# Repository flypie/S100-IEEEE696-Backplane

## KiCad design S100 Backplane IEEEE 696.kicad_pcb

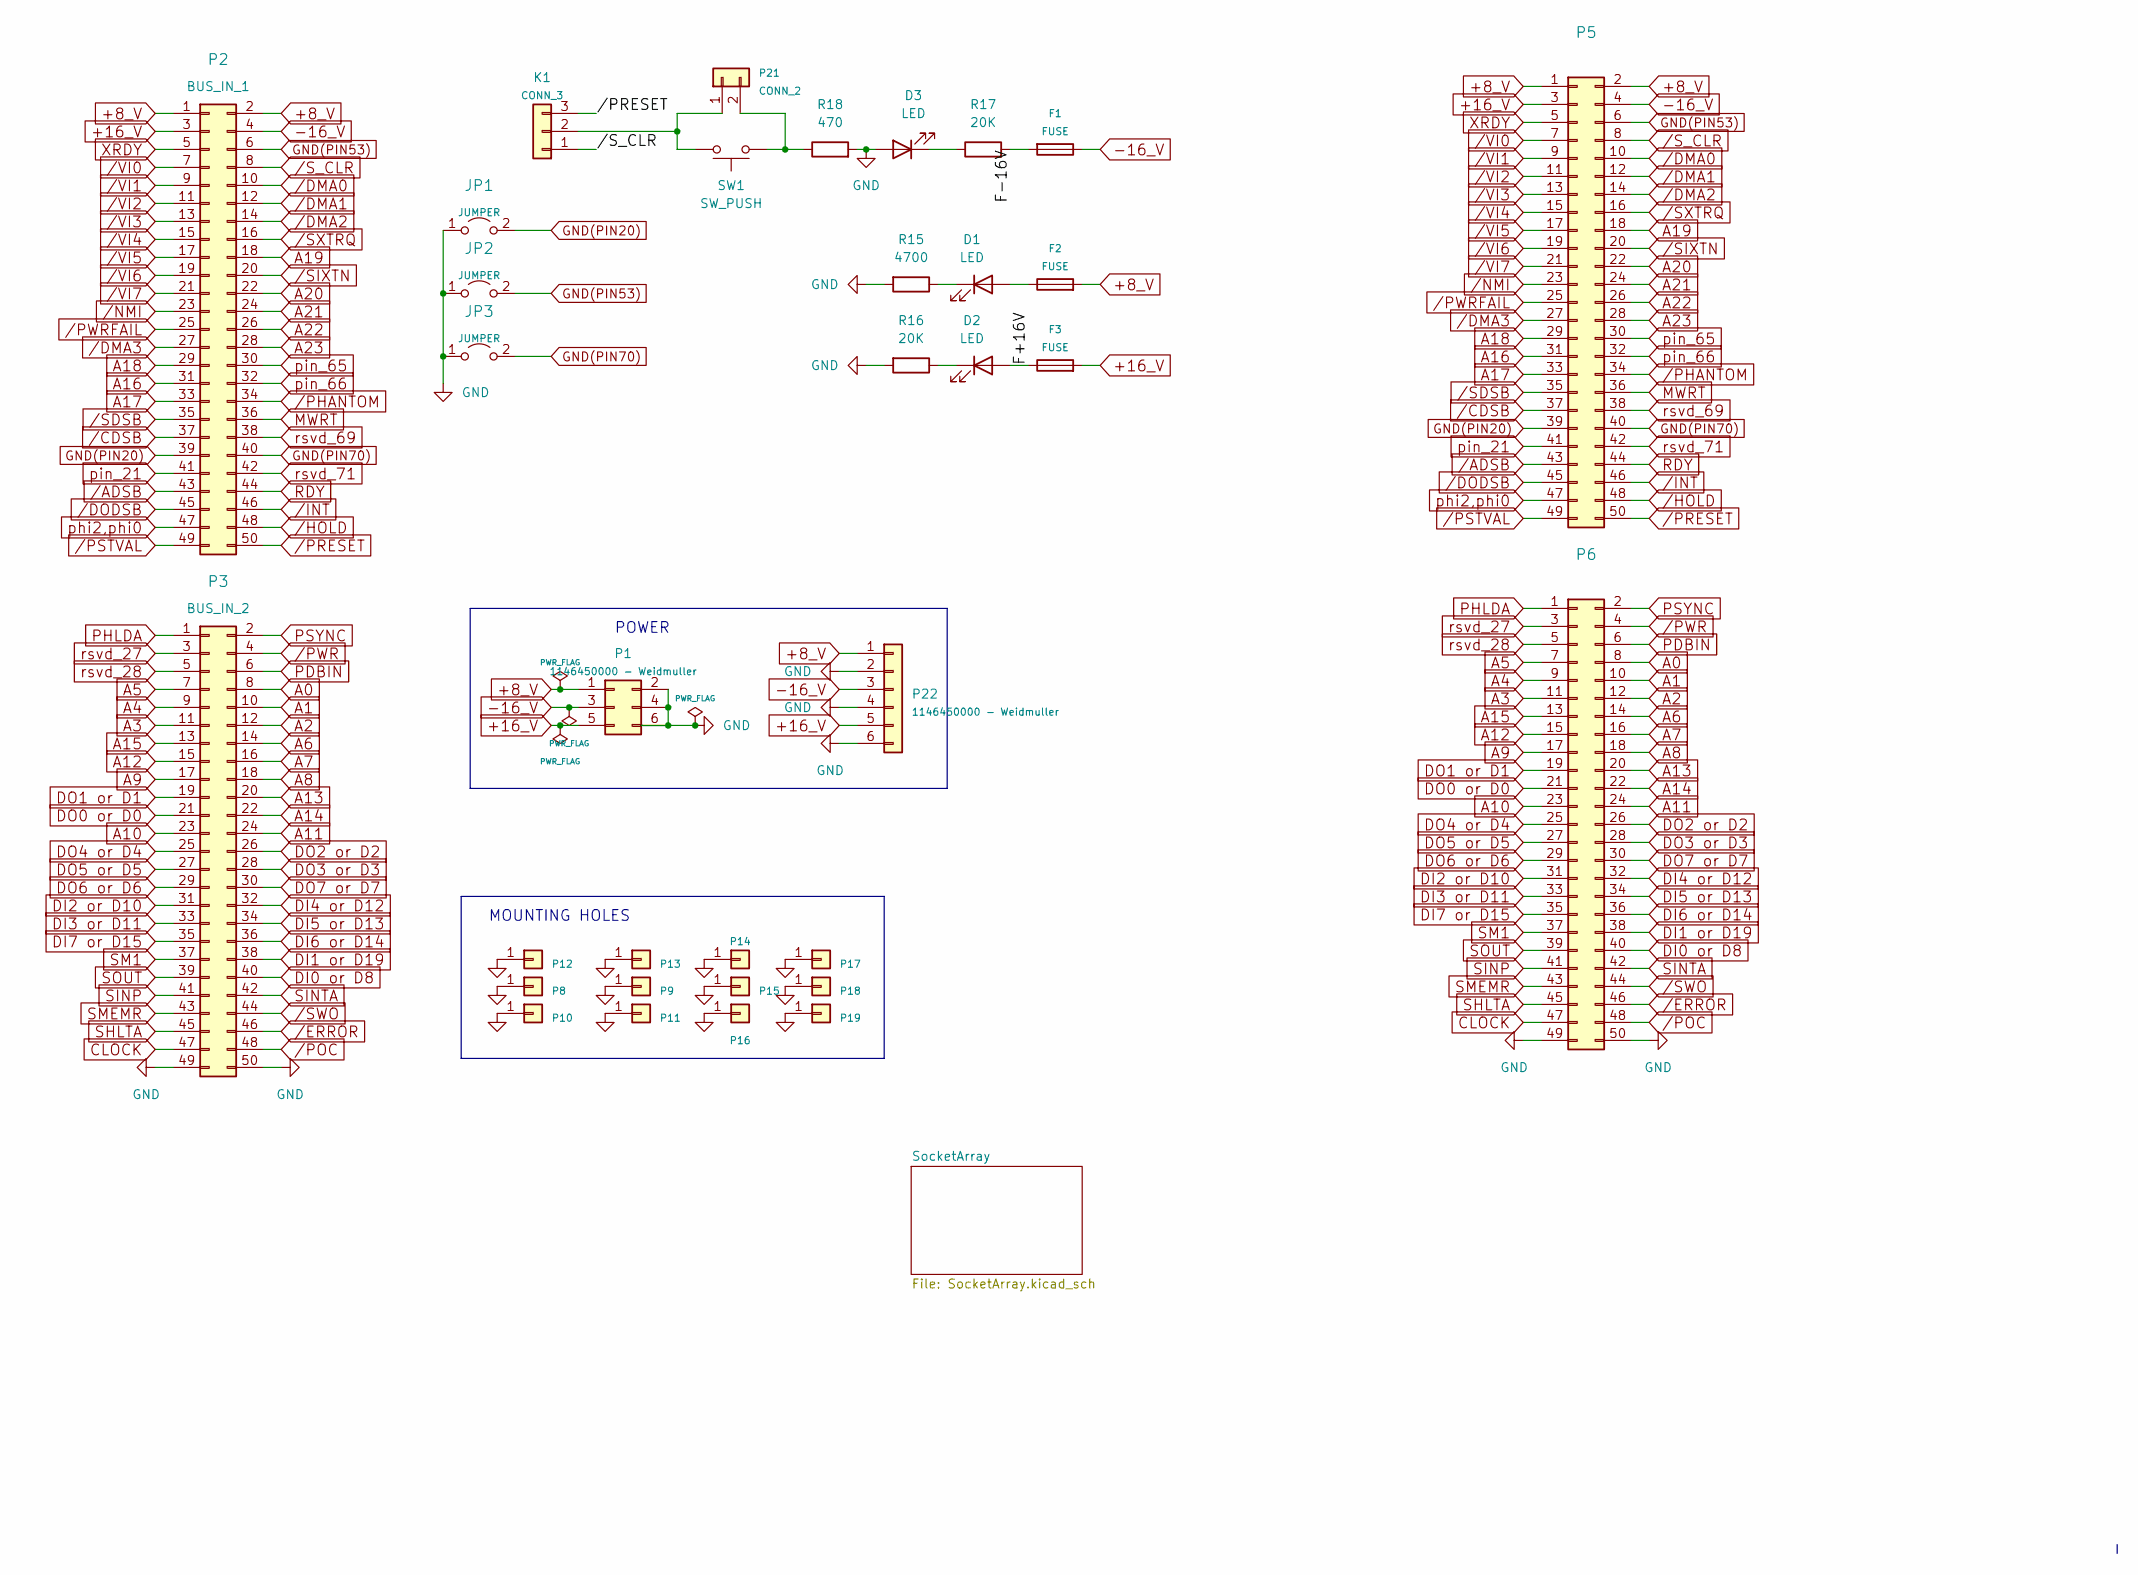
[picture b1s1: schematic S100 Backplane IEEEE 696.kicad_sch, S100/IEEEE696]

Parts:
D1, D2, D3: LED; LED_D3.0mm
F1, F2, F3: FUSE; R_Axial_DIN0207_L6.3mm_D2.5mm_P10.16mm_Horizontal
JP1, JP2, JP3: JUMPER; PinHeader_1x02_P2.54mm_Vertical
K1: CONN_3; PinHeader_1x03_P2.54mm_Vertical
P1, P22: 1146450000 - Weidmuller; 1146450000
P2: BUS_IN_1; PinHeader_2x25_P2.54mm_Vertical
P3: BUS_IN_2; PinHeader_2x25_P2.54mm_Vertical
P5, P6: PinHeader_2x25_P2.54mm_Vertical
P8, P9, P10, P11, P12, P13, P14, P15, P16, P17, P18, P19: CONN_1; MountingHole_3.5mm_Pad
P21: CONN_2; PinHeader_1x02_P2.54mm_Vertical
R15: 4700; R_Axial_DIN0207_L6.3mm_D2.5mm_P10.16mm_Horizontal
R16, R17: 20K; R_Axial_DIN0207_L6.3mm_D2.5mm_P10.16mm_Horizontal
R18: 470; R_Axial_DIN0207_L6.3mm_D2.5mm_P7.62mm_Horizontal
SW1: SW_PUSH; SW_PUSH_6mm_H7.3mm

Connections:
+8_V: F2.2, P1.1, P2.1, P2.2, P5.1, P5.2, P22.1; also elsewhere on the board
+16_V: F3.2, P1.5, P2.3, P5.3, P22.5; also elsewhere on the board
-16_V: F1.1, P1.3, P2.4, P5.4, P22.3; also elsewhere on the board
/F+16V: D2.2 (A), F3.1
/F-16V: F1.2, R17.2
A0: P3.8, P6.8; also elsewhere on the board
A1: P3.10, P6.10; also elsewhere on the board
A2: P3.12, P6.12; also elsewhere on the board
A3: P3.11, P6.11; also elsewhere on the board
A4: P3.9, P6.9; also elsewhere on the board
A5: P3.7, P6.7; also elsewhere on the board
A6: P3.14, P6.14; also elsewhere on the board
A7: P3.16, P6.16; also elsewhere on the board
A8: P3.18, P6.18; also elsewhere on the board
A9: P3.17, P6.17; also elsewhere on the board
A10: P3.23, P6.23; also elsewhere on the board
A11: P3.24, P6.24; also elsewhere on the board
A12: P3.15, P6.15; also elsewhere on the board
A13: P3.20, P6.20; also elsewhere on the board
A14: P3.22, P6.22; also elsewhere on the board
A15: P3.13, P6.13; also elsewhere on the board
A16: P2.31, P5.31; also elsewhere on the board
A17: P2.33, P5.33; also elsewhere on the board
A18: P2.29, P5.29; also elsewhere on the board
A19: P2.18, P5.18; also elsewhere on the board
A20: P2.22, P5.22; also elsewhere on the board
A21: P2.24, P5.24; also elsewhere on the board
A22: P2.26, P5.26; also elsewhere on the board
A23: P2.28, P5.28; also elsewhere on the board
CLOCK: P3.47, P6.47; also elsewhere on the board
DI0 or D8: P3.40, P6.40; also elsewhere on the board
DI1 or D19: P3.38, P6.38; also elsewhere on the board
DI2 or D10: P3.31, P6.31; also elsewhere on the board
DI3 or D11: P3.33, P6.33; also elsewhere on the board
DI4 or D12: P3.32, P6.32; also elsewhere on the board
DI5 or D13: P3.34, P6.34; also elsewhere on the board
DI6 or D14: P3.36, P6.36; also elsewhere on the board
DI7 or D15: P3.35, P6.35; also elsewhere on the board
DO0 or D0: P3.21, P6.21; also elsewhere on the board
DO1 or D1: P3.19, P6.19; also elsewhere on the board
DO2 or D2: P3.26, P6.26; also elsewhere on the board
DO3 or D3: P3.28, P6.28; also elsewhere on the board
DO4 or D4: P3.25, P6.25; also elsewhere on the board
DO5 or D5: P3.27, P6.27; also elsewhere on the board
DO6 or D6: P3.29, P6.29; also elsewhere on the board
DO7 or D7: P3.30, P6.30; also elsewhere on the board
GND(PIN20): JP1.2 (B), P2.39, P5.39; also elsewhere on the board
GND(PIN53): JP2.2 (B), P2.6, P5.6; also elsewhere on the board
GND(PIN70): JP3.2 (B), P2.40, P5.40; also elsewhere on the board
MWRT: P2.36, P5.36; also elsewhere on the board
unnamed: D1.1 (K), R15.1
unnamed: D1.2 (A), F2.1
unnamed: D2.1 (K), R16.1
unnamed: D3.1 (K), R17.1
unnamed: K1.2, P21.1, SW1.2
unnamed: P21.2, R18.1, SW1.1
PDBIN: P3.6, P6.6; also elsewhere on the board
PHLDA: P3.1, P6.1; also elsewhere on the board
PSYNC: P3.2, P6.2; also elsewhere on the board
RDY: P2.44, P5.44; also elsewhere on the board
SHLTA: P3.45, P6.45; also elsewhere on the board
SINP: P3.41, P6.41; also elsewhere on the board
SINTA: P3.42, P6.42; also elsewhere on the board
SM1: P3.37, P6.37; also elsewhere on the board
SMEMR: P3.43, P6.43; also elsewhere on the board
SOUT: P3.39, P6.39; also elsewhere on the board
XRDY: P2.5, P5.5; also elsewhere on the board
phi2,phi0: P2.47, P5.47; also elsewhere on the board
pin_21: P2.41, P5.41; also elsewhere on the board
pin_65: P2.30, P5.30; also elsewhere on the board
pin_66: P2.32, P5.32; also elsewhere on the board
rsvd_27: P3.3, P6.3; also elsewhere on the board
rsvd_28: P3.5, P6.5; also elsewhere on the board
rsvd_69: P2.38, P5.38; also elsewhere on the board
rsvd_71: P2.42, P5.42; also elsewhere on the board
/ADSB: P2.43, P5.43; also elsewhere on the board
/CDSB: P2.37, P5.37; also elsewhere on the board
/DMA0: P2.10, P5.10; also elsewhere on the board
/DMA1: P2.12, P5.12; also elsewhere on the board
/DMA2: P2.14, P5.14; also elsewhere on the board
/DMA3: P2.27, P5.27; also elsewhere on the board
/DODSB: P2.45, P5.45; also elsewhere on the board
/ERROR: P3.46, P6.46; also elsewhere on the board
/HOLD: P2.48, P5.48; also elsewhere on the board
/INT: P2.46, P5.46; also elsewhere on the board
/NMI: P2.23, P5.23; also elsewhere on the board
/PHANTOM: P2.34, P5.34; also elsewhere on the board
/POC: P3.48, P6.48; also elsewhere on the board
/PRESET: K1.3, P2.50, P5.50; also elsewhere on the board
/PSTVAL: P2.49, P5.49; also elsewhere on the board
/PWR: P3.4, P6.4; also elsewhere on the board
/PWRFAIL: P2.25, P5.25; also elsewhere on the board
/SDSB: P2.35, P5.35; also elsewhere on the board
/SIXTN: P2.20, P5.20; also elsewhere on the board
/SWO: P3.44, P6.44; also elsewhere on the board
/SXTRQ: P2.16, P5.16; also elsewhere on the board
/S_CLR: K1.1, P2.8, P5.8; also elsewhere on the board
/VI0: P2.7, P5.7; also elsewhere on the board
/VI1: P2.9, P5.9; also elsewhere on the board
/VI2: P2.11, P5.11; also elsewhere on the board
/VI3: P2.13, P5.13; also elsewhere on the board
/VI4: P2.15, P5.15; also elsewhere on the board
/VI5: P2.17, P5.17; also elsewhere on the board
/VI6: P2.19, P5.19; also elsewhere on the board
/VI7: P2.21, P5.21; also elsewhere on the board

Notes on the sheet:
POWER
MOUNTING HOLES

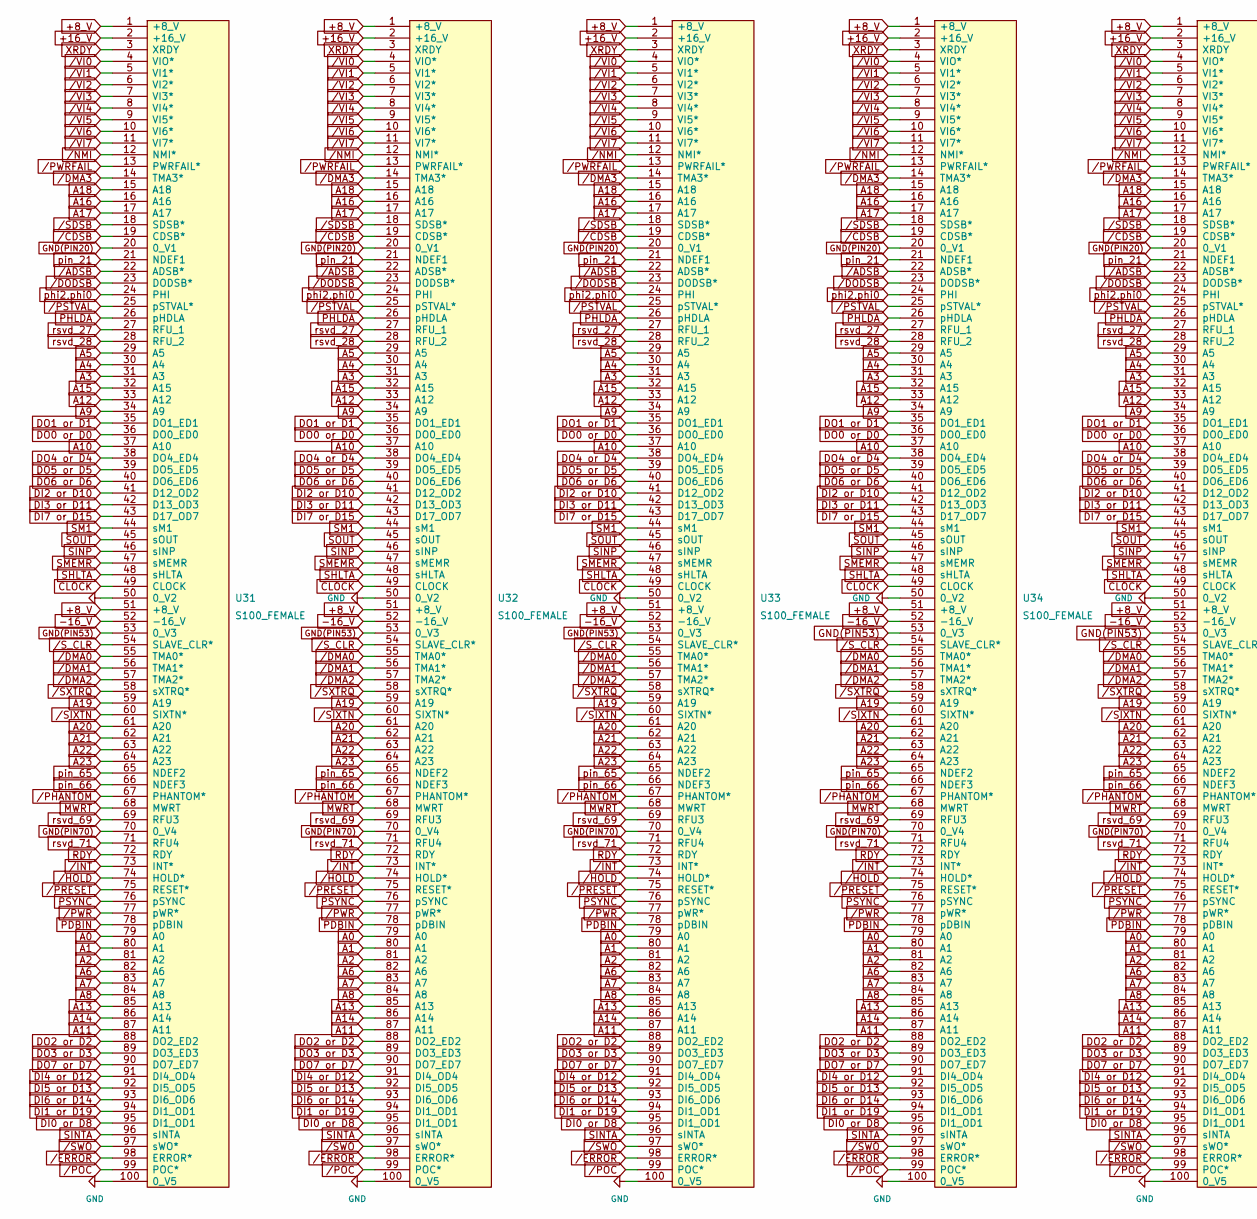
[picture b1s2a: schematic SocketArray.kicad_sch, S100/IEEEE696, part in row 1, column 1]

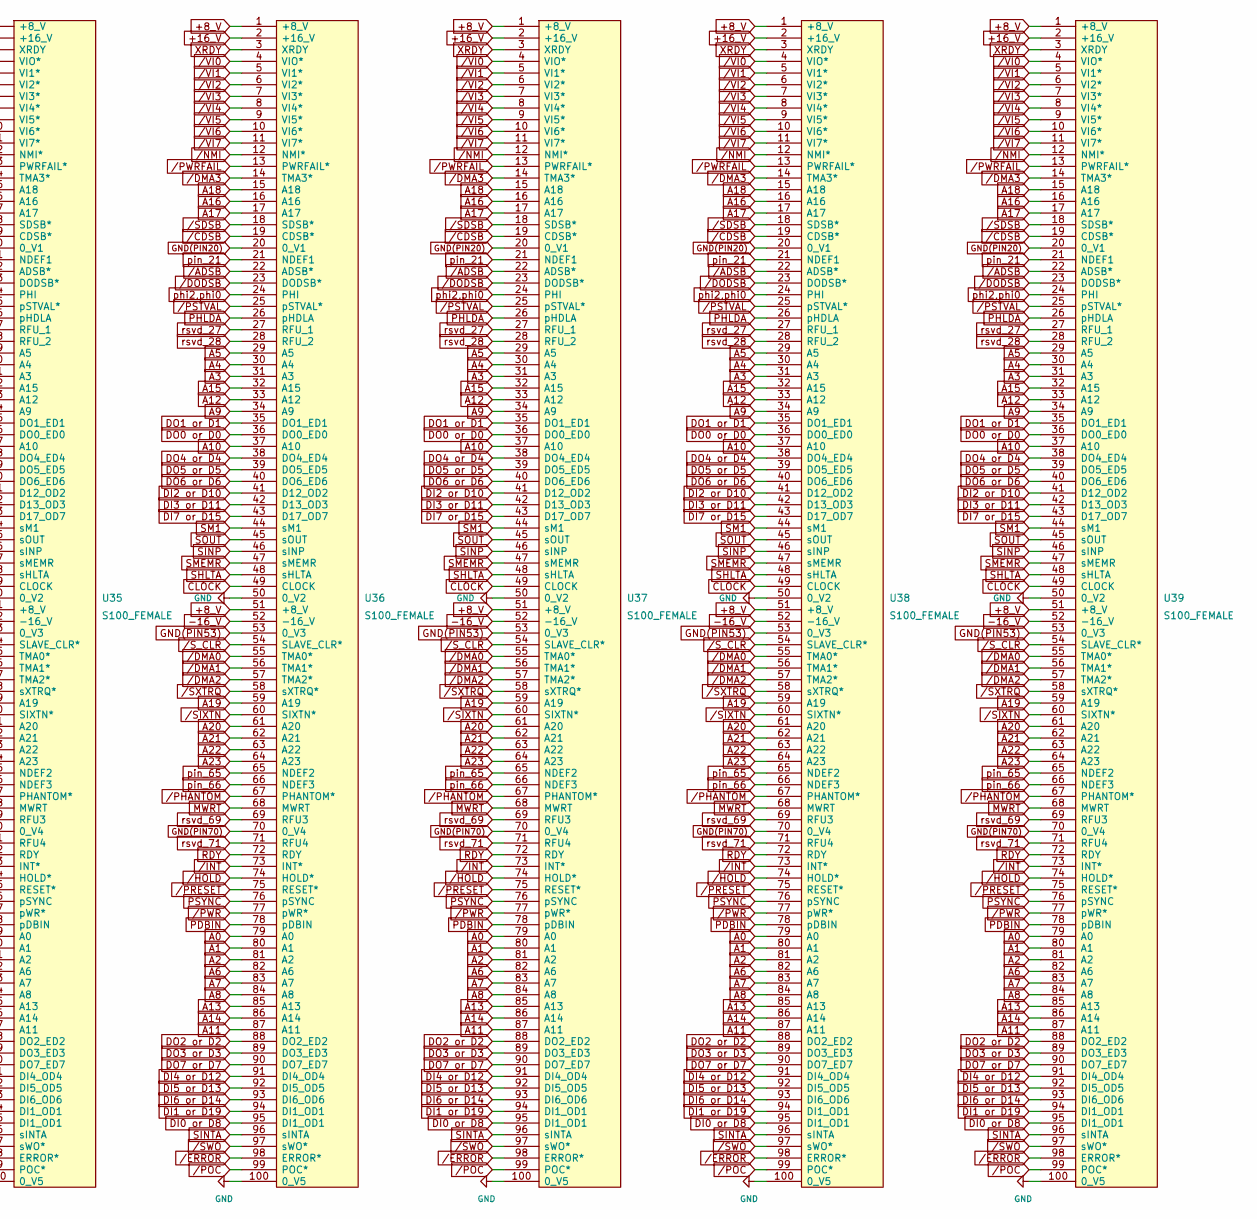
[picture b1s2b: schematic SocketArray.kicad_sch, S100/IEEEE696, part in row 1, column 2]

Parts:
U31, U32, U33, U34, U35, U36, U37, U38, U39: S100_FEMALE

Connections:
+8_V: U31.1 (+8_V), U31.51 (+8_V), U32.1 (+8_V), U32.51 (+8_V), U33.1 (+8_V), U33.51 (+8_V), U34.1 (+8_V), U34.51 (+8_V), U35.1 (+8_V), U35.51 (+8_V), U36.1 (+8_V), U36.51 (+8_V), U37.1 (+8_V), U37.51 (+8_V), U38.1 (+8_V), U38.51 (+8_V), U39.1 (+8_V), U39.51 (+8_V); also elsewhere on the board
+16_V: U31.2 (+16_V), U32.2 (+16_V), U33.2 (+16_V), U34.2 (+16_V), U35.2 (+16_V), U36.2 (+16_V), U37.2 (+16_V), U38.2 (+16_V), U39.2 (+16_V); also elsewhere on the board
-16_V: U31.52 (-16_V), U32.52 (-16_V), U33.52 (-16_V), U34.52 (-16_V), U35.52 (-16_V), U36.52 (-16_V), U37.52 (-16_V), U38.52 (-16_V), U39.52 (-16_V); also elsewhere on the board
A0: U31.79 (A0), U32.79 (A0), U33.79 (A0), U34.79 (A0), U35.79 (A0), U36.79 (A0), U37.79 (A0), U38.79 (A0), U39.79 (A0); also elsewhere on the board
A1: U31.80 (A1), U32.80 (A1), U33.80 (A1), U34.80 (A1), U35.80 (A1), U36.80 (A1), U37.80 (A1), U38.80 (A1), U39.80 (A1); also elsewhere on the board
A2: U31.81 (A2), U32.81 (A2), U33.81 (A2), U34.81 (A2), U35.81 (A2), U36.81 (A2), U37.81 (A2), U38.81 (A2), U39.81 (A2); also elsewhere on the board
A3: U31.31 (A3), U32.31 (A3), U33.31 (A3), U34.31 (A3), U35.31 (A3), U36.31 (A3), U37.31 (A3), U38.31 (A3), U39.31 (A3); also elsewhere on the board
A4: U31.30 (A4), U32.30 (A4), U33.30 (A4), U34.30 (A4), U35.30 (A4), U36.30 (A4), U37.30 (A4), U38.30 (A4), U39.30 (A4); also elsewhere on the board
A5: U31.29 (A5), U32.29 (A5), U33.29 (A5), U34.29 (A5), U35.29 (A5), U36.29 (A5), U37.29 (A5), U38.29 (A5), U39.29 (A5); also elsewhere on the board
A6: U31.82 (A6), U32.82 (A6), U33.82 (A6), U34.82 (A6), U35.82 (A6), U36.82 (A6), U37.82 (A6), U38.82 (A6), U39.82 (A6); also elsewhere on the board
A7: U31.83 (A7), U32.83 (A7), U33.83 (A7), U34.83 (A7), U35.83 (A7), U36.83 (A7), U37.83 (A7), U38.83 (A7), U39.83 (A7); also elsewhere on the board
A8: U31.84 (A8), U32.84 (A8), U33.84 (A8), U34.84 (A8), U35.84 (A8), U36.84 (A8), U37.84 (A8), U38.84 (A8), U39.84 (A8); also elsewhere on the board
A9: U31.34 (A9), U32.34 (A9), U33.34 (A9), U34.34 (A9), U35.34 (A9), U36.34 (A9), U37.34 (A9), U38.34 (A9), U39.34 (A9); also elsewhere on the board
A10: U31.37 (A10), U32.37 (A10), U33.37 (A10), U34.37 (A10), U35.37 (A10), U36.37 (A10), U37.37 (A10), U38.37 (A10), U39.37 (A10); also elsewhere on the board
A11: U31.87 (A11), U32.87 (A11), U33.87 (A11), U34.87 (A11), U35.87 (A11), U36.87 (A11), U37.87 (A11), U38.87 (A11), U39.87 (A11); also elsewhere on the board
A12: U31.33 (A12), U32.33 (A12), U33.33 (A12), U34.33 (A12), U35.33 (A12), U36.33 (A12), U37.33 (A12), U38.33 (A12), U39.33 (A12); also elsewhere on the board
A13: U31.85 (A13), U32.85 (A13), U33.85 (A13), U34.85 (A13), U35.85 (A13), U36.85 (A13), U37.85 (A13), U38.85 (A13), U39.85 (A13); also elsewhere on the board
A14: U31.86 (A14), U32.86 (A14), U33.86 (A14), U34.86 (A14), U35.86 (A14), U36.86 (A14), U37.86 (A14), U38.86 (A14), U39.86 (A14); also elsewhere on the board
A15: U31.32 (A15), U32.32 (A15), U33.32 (A15), U34.32 (A15), U35.32 (A15), U36.32 (A15), U37.32 (A15), U38.32 (A15), U39.32 (A15); also elsewhere on the board
A16: U31.16 (A16), U32.16 (A16), U33.16 (A16), U34.16 (A16), U35.16 (A16), U36.16 (A16), U37.16 (A16), U38.16 (A16), U39.16 (A16); also elsewhere on the board
A17: U31.17 (A17), U32.17 (A17), U33.17 (A17), U34.17 (A17), U35.17 (A17), U36.17 (A17), U37.17 (A17), U38.17 (A17), U39.17 (A17); also elsewhere on the board
A18: U31.15 (A18), U32.15 (A18), U33.15 (A18), U34.15 (A18), U35.15 (A18), U36.15 (A18), U37.15 (A18), U38.15 (A18), U39.15 (A18); also elsewhere on the board
A19: U31.59 (A19), U32.59 (A19), U33.59 (A19), U34.59 (A19), U35.59 (A19), U36.59 (A19), U37.59 (A19), U38.59 (A19), U39.59 (A19); also elsewhere on the board
A20: U31.61 (A20), U32.61 (A20), U33.61 (A20), U34.61 (A20), U35.61 (A20), U36.61 (A20), U37.61 (A20), U38.61 (A20), U39.61 (A20); also elsewhere on the board
A21: U31.62 (A21), U32.62 (A21), U33.62 (A21), U34.62 (A21), U35.62 (A21), U36.62 (A21), U37.62 (A21), U38.62 (A21), U39.62 (A21); also elsewhere on the board
A22: U31.63 (A22), U32.63 (A22), U33.63 (A22), U34.63 (A22), U35.63 (A22), U36.63 (A22), U37.63 (A22), U38.63 (A22), U39.63 (A22); also elsewhere on the board
A23: U31.64 (A23), U32.64 (A23), U33.64 (A23), U34.64 (A23), U35.64 (A23), U36.64 (A23), U37.64 (A23), U38.64 (A23), U39.64 (A23); also elsewhere on the board
CLOCK: U31.49 (CLOCK), U32.49 (CLOCK), U33.49 (CLOCK), U34.49 (CLOCK), U35.49 (CLOCK), U36.49 (CLOCK), U37.49 (CLOCK), U38.49 (CLOCK), U39.49 (CLOCK); also elsewhere on the board
DI0 or D8: U31.95 (DI1_OD1), U32.95 (DI1_OD1), U33.95 (DI1_OD1), U34.95 (DI1_OD1), U35.95 (DI1_OD1), U36.95 (DI1_OD1), U37.95 (DI1_OD1), U38.95 (DI1_OD1), U39.95 (DI1_OD1); also elsewhere on the board
DI1 or D19: U31.94 (DI1_OD1), U32.94 (DI1_OD1), U33.94 (DI1_OD1), U34.94 (DI1_OD1), U35.94 (DI1_OD1), U36.94 (DI1_OD1), U37.94 (DI1_OD1), U38.94 (DI1_OD1), U39.94 (DI1_OD1); also elsewhere on the board
DI2 or D10: U31.41 (D12_OD2), U32.41 (D12_OD2), U33.41 (D12_OD2), U34.41 (D12_OD2), U35.41 (D12_OD2), U36.41 (D12_OD2), U37.41 (D12_OD2), U38.41 (D12_OD2), U39.41 (D12_OD2); also elsewhere on the board
DI3 or D11: U31.42 (D13_OD3), U32.42 (D13_OD3), U33.42 (D13_OD3), U34.42 (D13_OD3), U35.42 (D13_OD3), U36.42 (D13_OD3), U37.42 (D13_OD3), U38.42 (D13_OD3), U39.42 (D13_OD3); also elsewhere on the board
DI4 or D12: U31.91 (DI4_OD4), U32.91 (DI4_OD4), U33.91 (DI4_OD4), U34.91 (DI4_OD4), U35.91 (DI4_OD4), U36.91 (DI4_OD4), U37.91 (DI4_OD4), U38.91 (DI4_OD4), U39.91 (DI4_OD4); also elsewhere on the board
DI5 or D13: U31.92 (DI5_OD5), U32.92 (DI5_OD5), U33.92 (DI5_OD5), U34.92 (DI5_OD5), U35.92 (DI5_OD5), U36.92 (DI5_OD5), U37.92 (DI5_OD5), U38.92 (DI5_OD5), U39.92 (DI5_OD5); also elsewhere on the board
DI6 or D14: U31.93 (DI6_OD6), U32.93 (DI6_OD6), U33.93 (DI6_OD6), U34.93 (DI6_OD6), U35.93 (DI6_OD6), U36.93 (DI6_OD6), U37.93 (DI6_OD6), U38.93 (DI6_OD6), U39.93 (DI6_OD6); also elsewhere on the board
DI7 or D15: U31.43 (D17_OD7), U32.43 (D17_OD7), U33.43 (D17_OD7), U34.43 (D17_OD7), U35.43 (D17_OD7), U36.43 (D17_OD7), U37.43 (D17_OD7), U38.43 (D17_OD7), U39.43 (D17_OD7); also elsewhere on the board
DO0 or D0: U31.36 (DO0_ED0), U32.36 (DO0_ED0), U33.36 (DO0_ED0), U34.36 (DO0_ED0), U35.36 (DO0_ED0), U36.36 (DO0_ED0), U37.36 (DO0_ED0), U38.36 (DO0_ED0), U39.36 (DO0_ED0); also elsewhere on the board
DO1 or D1: U31.35 (DO1_ED1), U32.35 (DO1_ED1), U33.35 (DO1_ED1), U34.35 (DO1_ED1), U35.35 (DO1_ED1), U36.35 (DO1_ED1), U37.35 (DO1_ED1), U38.35 (DO1_ED1), U39.35 (DO1_ED1); also elsewhere on the board
DO2 or D2: U31.88 (DO2_ED2), U32.88 (DO2_ED2), U33.88 (DO2_ED2), U34.88 (DO2_ED2), U35.88 (DO2_ED2), U36.88 (DO2_ED2), U37.88 (DO2_ED2), U38.88 (DO2_ED2), U39.88 (DO2_ED2); also elsewhere on the board
DO3 or D3: U31.89 (DO3_ED3), U32.89 (DO3_ED3), U33.89 (DO3_ED3), U34.89 (DO3_ED3), U35.89 (DO3_ED3), U36.89 (DO3_ED3), U37.89 (DO3_ED3), U38.89 (DO3_ED3), U39.89 (DO3_ED3); also elsewhere on the board
DO4 or D4: U31.38 (DO4_ED4), U32.38 (DO4_ED4), U33.38 (DO4_ED4), U34.38 (DO4_ED4), U35.38 (DO4_ED4), U36.38 (DO4_ED4), U37.38 (DO4_ED4), U38.38 (DO4_ED4), U39.38 (DO4_ED4); also elsewhere on the board
DO5 or D5: U31.39 (DO5_ED5), U32.39 (DO5_ED5), U33.39 (DO5_ED5), U34.39 (DO5_ED5), U35.39 (DO5_ED5), U36.39 (DO5_ED5), U37.39 (DO5_ED5), U38.39 (DO5_ED5), U39.39 (DO5_ED5); also elsewhere on the board
DO6 or D6: U31.40 (DO6_ED6), U32.40 (DO6_ED6), U33.40 (DO6_ED6), U34.40 (DO6_ED6), U35.40 (DO6_ED6), U36.40 (DO6_ED6), U37.40 (DO6_ED6), U38.40 (DO6_ED6), U39.40 (DO6_ED6); also elsewhere on the board
DO7 or D7: U31.90 (DO7_ED7), U32.90 (DO7_ED7), U33.90 (DO7_ED7), U34.90 (DO7_ED7), U35.90 (DO7_ED7), U36.90 (DO7_ED7), U37.90 (DO7_ED7), U38.90 (DO7_ED7), U39.90 (DO7_ED7); also elsewhere on the board
GND(PIN20): U31.20 (0_V1), U32.20 (0_V1), U33.20 (0_V1), U34.20 (0_V1), U35.20 (0_V1), U36.20 (0_V1), U37.20 (0_V1), U38.20 (0_V1), U39.20 (0_V1); also elsewhere on the board
GND(PIN53): U31.53 (0_V3), U32.53 (0_V3), U33.53 (0_V3), U34.53 (0_V3), U35.53 (0_V3), U36.53 (0_V3), U37.53 (0_V3), U38.53 (0_V3), U39.53 (0_V3); also elsewhere on the board
GND(PIN70): U31.70 (0_V4), U32.70 (0_V4), U33.70 (0_V4), U34.70 (0_V4), U35.70 (0_V4), U36.70 (0_V4), U37.70 (0_V4), U38.70 (0_V4), U39.70 (0_V4); also elsewhere on the board
MWRT: U31.68 (MWRT), U32.68 (MWRT), U33.68 (MWRT), U34.68 (MWRT), U35.68 (MWRT), U36.68 (MWRT), U37.68 (MWRT), U38.68 (MWRT), U39.68 (MWRT); also elsewhere on the board
PDBIN: U31.78 (pDBIN), U32.78 (pDBIN), U33.78 (pDBIN), U34.78 (pDBIN), U35.78 (pDBIN), U36.78 (pDBIN), U37.78 (pDBIN), U38.78 (pDBIN), U39.78 (pDBIN); also elsewhere on the board
PHLDA: U31.26 (pHDLA), U32.26 (pHDLA), U33.26 (pHDLA), U34.26 (pHDLA), U35.26 (pHDLA), U36.26 (pHDLA), U37.26 (pHDLA), U38.26 (pHDLA), U39.26 (pHDLA); also elsewhere on the board
PSYNC: U31.76 (pSYNC), U32.76 (pSYNC), U33.76 (pSYNC), U34.76 (pSYNC), U35.76 (pSYNC), U36.76 (pSYNC), U37.76 (pSYNC), U38.76 (pSYNC), U39.76 (pSYNC); also elsewhere on the board
RDY: U31.72 (RDY), U32.72 (RDY), U33.72 (RDY), U34.72 (RDY), U35.72 (RDY), U36.72 (RDY), U37.72 (RDY), U38.72 (RDY), U39.72 (RDY); also elsewhere on the board
SHLTA: U31.48 (sHLTA), U32.48 (sHLTA), U33.48 (sHLTA), U34.48 (sHLTA), U35.48 (sHLTA), U36.48 (sHLTA), U37.48 (sHLTA), U38.48 (sHLTA), U39.48 (sHLTA); also elsewhere on the board
SINP: U31.46 (sINP), U32.46 (sINP), U33.46 (sINP), U34.46 (sINP), U35.46 (sINP), U36.46 (sINP), U37.46 (sINP), U38.46 (sINP), U39.46 (sINP); also elsewhere on the board
SINTA: U31.96 (sINTA), U32.96 (sINTA), U33.96 (sINTA), U34.96 (sINTA), U35.96 (sINTA), U36.96 (sINTA), U37.96 (sINTA), U38.96 (sINTA), U39.96 (sINTA); also elsewhere on the board
SM1: U31.44 (sM1), U32.44 (sM1), U33.44 (sM1), U34.44 (sM1), U35.44 (sM1), U36.44 (sM1), U37.44 (sM1), U38.44 (sM1), U39.44 (sM1); also elsewhere on the board
SMEMR: U31.47 (sMEMR), U32.47 (sMEMR), U33.47 (sMEMR), U34.47 (sMEMR), U35.47 (sMEMR), U36.47 (sMEMR), U37.47 (sMEMR), U38.47 (sMEMR), U39.47 (sMEMR); also elsewhere on the board
SOUT: U31.45 (sOUT), U32.45 (sOUT), U33.45 (sOUT), U34.45 (sOUT), U35.45 (sOUT), U36.45 (sOUT), U37.45 (sOUT), U38.45 (sOUT), U39.45 (sOUT); also elsewhere on the board
XRDY: U31.3 (XRDY), U32.3 (XRDY), U33.3 (XRDY), U34.3 (XRDY), U35.3 (XRDY), U36.3 (XRDY), U37.3 (XRDY), U38.3 (XRDY), U39.3 (XRDY); also elsewhere on the board
phi2,phi0: U31.24 (PHI), U32.24 (PHI), U33.24 (PHI), U34.24 (PHI), U35.24 (PHI), U36.24 (PHI), U37.24 (PHI), U38.24 (PHI), U39.24 (PHI); also elsewhere on the board
pin_21: U31.21 (NDEF1), U32.21 (NDEF1), U33.21 (NDEF1), U34.21 (NDEF1), U35.21 (NDEF1), U36.21 (NDEF1), U37.21 (NDEF1), U38.21 (NDEF1), U39.21 (NDEF1); also elsewhere on the board
pin_65: U31.65 (NDEF2), U32.65 (NDEF2), U33.65 (NDEF2), U34.65 (NDEF2), U35.65 (NDEF2), U36.65 (NDEF2), U37.65 (NDEF2), U38.65 (NDEF2), U39.65 (NDEF2); also elsewhere on the board
pin_66: U31.66 (NDEF3), U32.66 (NDEF3), U33.66 (NDEF3), U34.66 (NDEF3), U35.66 (NDEF3), U36.66 (NDEF3), U37.66 (NDEF3), U38.66 (NDEF3), U39.66 (NDEF3); also elsewhere on the board
rsvd_27: U31.27 (RFU_1), U32.27 (RFU_1), U33.27 (RFU_1), U34.27 (RFU_1), U35.27 (RFU_1), U36.27 (RFU_1), U37.27 (RFU_1), U38.27 (RFU_1), U39.27 (RFU_1); also elsewhere on the board
rsvd_28: U31.28 (RFU_2), U32.28 (RFU_2), U33.28 (RFU_2), U34.28 (RFU_2), U35.28 (RFU_2), U36.28 (RFU_2), U37.28 (RFU_2), U38.28 (RFU_2), U39.28 (RFU_2); also elsewhere on the board
rsvd_69: U31.69 (RFU3), U32.69 (RFU3), U33.69 (RFU3), U34.69 (RFU3), U35.69 (RFU3), U36.69 (RFU3), U37.69 (RFU3), U38.69 (RFU3), U39.69 (RFU3); also elsewhere on the board
rsvd_71: U31.71 (RFU4), U32.71 (RFU4), U33.71 (RFU4), U34.71 (RFU4), U35.71 (RFU4), U36.71 (RFU4), U37.71 (RFU4), U38.71 (RFU4), U39.71 (RFU4); also elsewhere on the board
/ADSB: U31.22 (ADSB*), U32.22 (ADSB*), U33.22 (ADSB*), U34.22 (ADSB*), U35.22 (ADSB*), U36.22 (ADSB*), U37.22 (ADSB*), U38.22 (ADSB*), U39.22 (ADSB*); also elsewhere on the board
/CDSB: U31.19 (CDSB*), U32.19 (CDSB*), U33.19 (CDSB*), U34.19 (CDSB*), U35.19 (CDSB*), U36.19 (CDSB*), U37.19 (CDSB*), U38.19 (CDSB*), U39.19 (CDSB*); also elsewhere on the board
/DMA0: U31.55 (TMA0*), U32.55 (TMA0*), U33.55 (TMA0*), U34.55 (TMA0*), U35.55 (TMA0*), U36.55 (TMA0*), U37.55 (TMA0*), U38.55 (TMA0*), U39.55 (TMA0*); also elsewhere on the board
/DMA1: U31.56 (TMA1*), U32.56 (TMA1*), U33.56 (TMA1*), U34.56 (TMA1*), U35.56 (TMA1*), U36.56 (TMA1*), U37.56 (TMA1*), U38.56 (TMA1*), U39.56 (TMA1*); also elsewhere on the board
/DMA2: U31.57 (TMA2*), U32.57 (TMA2*), U33.57 (TMA2*), U34.57 (TMA2*), U35.57 (TMA2*), U36.57 (TMA2*), U37.57 (TMA2*), U38.57 (TMA2*), U39.57 (TMA2*); also elsewhere on the board
/DMA3: U31.14 (TMA3*), U32.14 (TMA3*), U33.14 (TMA3*), U34.14 (TMA3*), U35.14 (TMA3*), U36.14 (TMA3*), U37.14 (TMA3*), U38.14 (TMA3*), U39.14 (TMA3*); also elsewhere on the board
/DODSB: U31.23 (DODSB*), U32.23 (DODSB*), U33.23 (DODSB*), U34.23 (DODSB*), U35.23 (DODSB*), U36.23 (DODSB*), U37.23 (DODSB*), U38.23 (DODSB*), U39.23 (DODSB*); also elsewhere on the board
/ERROR: U31.98 (ERROR*), U32.98 (ERROR*), U33.98 (ERROR*), U34.98 (ERROR*), U35.98 (ERROR*), U36.98 (ERROR*), U37.98 (ERROR*), U38.98 (ERROR*), U39.98 (ERROR*); also elsewhere on the board
/HOLD: U31.74 (HOLD*), U32.74 (HOLD*), U33.74 (HOLD*), U34.74 (HOLD*), U35.74 (HOLD*), U36.74 (HOLD*), U37.74 (HOLD*), U38.74 (HOLD*), U39.74 (HOLD*); also elsewhere on the board
/INT: U31.73 (INT*), U32.73 (INT*), U33.73 (INT*), U34.73 (INT*), U35.73 (INT*), U36.73 (INT*), U37.73 (INT*), U38.73 (INT*), U39.73 (INT*); also elsewhere on the board
/NMI: U31.12 (NMI*), U32.12 (NMI*), U33.12 (NMI*), U34.12 (NMI*), U35.12 (NMI*), U36.12 (NMI*), U37.12 (NMI*), U38.12 (NMI*), U39.12 (NMI*); also elsewhere on the board
/PHANTOM: U31.67 (PHANTOM*), U32.67 (PHANTOM*), U33.67 (PHANTOM*), U34.67 (PHANTOM*), U35.67 (PHANTOM*), U36.67 (PHANTOM*), U37.67 (PHANTOM*), U38.67 (PHANTOM*), U39.67 (PHANTOM*); also elsewhere on the board
/POC: U31.99 (POC*), U32.99 (POC*), U33.99 (POC*), U34.99 (POC*), U35.99 (POC*), U36.99 (POC*), U37.99 (POC*), U38.99 (POC*), U39.99 (POC*); also elsewhere on the board
/PRESET: U31.75 (RESET*), U32.75 (RESET*), U33.75 (RESET*), U34.75 (RESET*), U35.75 (RESET*), U36.75 (RESET*), U37.75 (RESET*), U38.75 (RESET*), U39.75 (RESET*); also elsewhere on the board
/PSTVAL: U31.25 (pSTVAL*), U32.25 (pSTVAL*), U33.25 (pSTVAL*), U34.25 (pSTVAL*), U35.25 (pSTVAL*), U36.25 (pSTVAL*), U37.25 (pSTVAL*), U38.25 (pSTVAL*), U39.25 (pSTVAL*); also elsewhere on the board
/PWR: U31.77 (pWR*), U32.77 (pWR*), U33.77 (pWR*), U34.77 (pWR*), U35.77 (pWR*), U36.77 (pWR*), U37.77 (pWR*), U38.77 (pWR*), U39.77 (pWR*); also elsewhere on the board
/PWRFAIL: U31.13 (PWRFAIL*), U32.13 (PWRFAIL*), U33.13 (PWRFAIL*), U34.13 (PWRFAIL*), U35.13 (PWRFAIL*), U36.13 (PWRFAIL*), U37.13 (PWRFAIL*), U38.13 (PWRFAIL*), U39.13 (PWRFAIL*); also elsewhere on the board
/SDSB: U31.18 (SDSB*), U32.18 (SDSB*), U33.18 (SDSB*), U34.18 (SDSB*), U35.18 (SDSB*), U36.18 (SDSB*), U37.18 (SDSB*), U38.18 (SDSB*), U39.18 (SDSB*); also elsewhere on the board
/SIXTN: U31.60 (SIXTN*), U32.60 (SIXTN*), U33.60 (SIXTN*), U34.60 (SIXTN*), U35.60 (SIXTN*), U36.60 (SIXTN*), U37.60 (SIXTN*), U38.60 (SIXTN*), U39.60 (SIXTN*); also elsewhere on the board
/SWO: U31.97 (sWO*), U32.97 (sWO*), U33.97 (sWO*), U34.97 (sWO*), U35.97 (sWO*), U36.97 (sWO*), U37.97 (sWO*), U38.97 (sWO*), U39.97 (sWO*); also elsewhere on the board
/SXTRQ: U31.58 (sXTRQ*), U32.58 (sXTRQ*), U33.58 (sXTRQ*), U34.58 (sXTRQ*), U35.58 (sXTRQ*), U36.58 (sXTRQ*), U37.58 (sXTRQ*), U38.58 (sXTRQ*), U39.58 (sXTRQ*); also elsewhere on the board
/S_CLR: U31.54 (SLAVE_CLR*), U32.54 (SLAVE_CLR*), U33.54 (SLAVE_CLR*), U34.54 (SLAVE_CLR*), U35.54 (SLAVE_CLR*), U36.54 (SLAVE_CLR*), U37.54 (SLAVE_CLR*), U38.54 (SLAVE_CLR*), U39.54 (SLAVE_CLR*); also elsewhere on the board
/VI0: U31.4 (VIO*), U32.4 (VIO*), U33.4 (VIO*), U34.4 (VIO*), U35.4 (VIO*), U36.4 (VIO*), U37.4 (VIO*), U38.4 (VIO*), U39.4 (VIO*); also elsewhere on the board
/VI1: U31.5 (VI1*), U32.5 (VI1*), U33.5 (VI1*), U34.5 (VI1*), U35.5 (VI1*), U36.5 (VI1*), U37.5 (VI1*), U38.5 (VI1*), U39.5 (VI1*); also elsewhere on the board
/VI2: U31.6 (VI2*), U32.6 (VI2*), U33.6 (VI2*), U34.6 (VI2*), U35.6 (VI2*), U36.6 (VI2*), U37.6 (VI2*), U38.6 (VI2*), U39.6 (VI2*); also elsewhere on the board
/VI3: U31.7 (VI3*), U32.7 (VI3*), U33.7 (VI3*), U34.7 (VI3*), U35.7 (VI3*), U36.7 (VI3*), U37.7 (VI3*), U38.7 (VI3*), U39.7 (VI3*); also elsewhere on the board
/VI4: U31.8 (VI4*), U32.8 (VI4*), U33.8 (VI4*), U34.8 (VI4*), U35.8 (VI4*), U36.8 (VI4*), U37.8 (VI4*), U38.8 (VI4*), U39.8 (VI4*); also elsewhere on the board
/VI5: U31.9 (VI5*), U32.9 (VI5*), U33.9 (VI5*), U34.9 (VI5*), U35.9 (VI5*), U36.9 (VI5*), U37.9 (VI5*), U38.9 (VI5*), U39.9 (VI5*); also elsewhere on the board
/VI6: U31.10 (VI6*), U32.10 (VI6*), U33.10 (VI6*), U34.10 (VI6*), U35.10 (VI6*), U36.10 (VI6*), U37.10 (VI6*), U38.10 (VI6*), U39.10 (VI6*); also elsewhere on the board
/VI7: U31.11 (VI7*), U32.11 (VI7*), U33.11 (VI7*), U34.11 (VI7*), U35.11 (VI7*), U36.11 (VI7*), U37.11 (VI7*), U38.11 (VI7*), U39.11 (VI7*); also elsewhere on the board

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
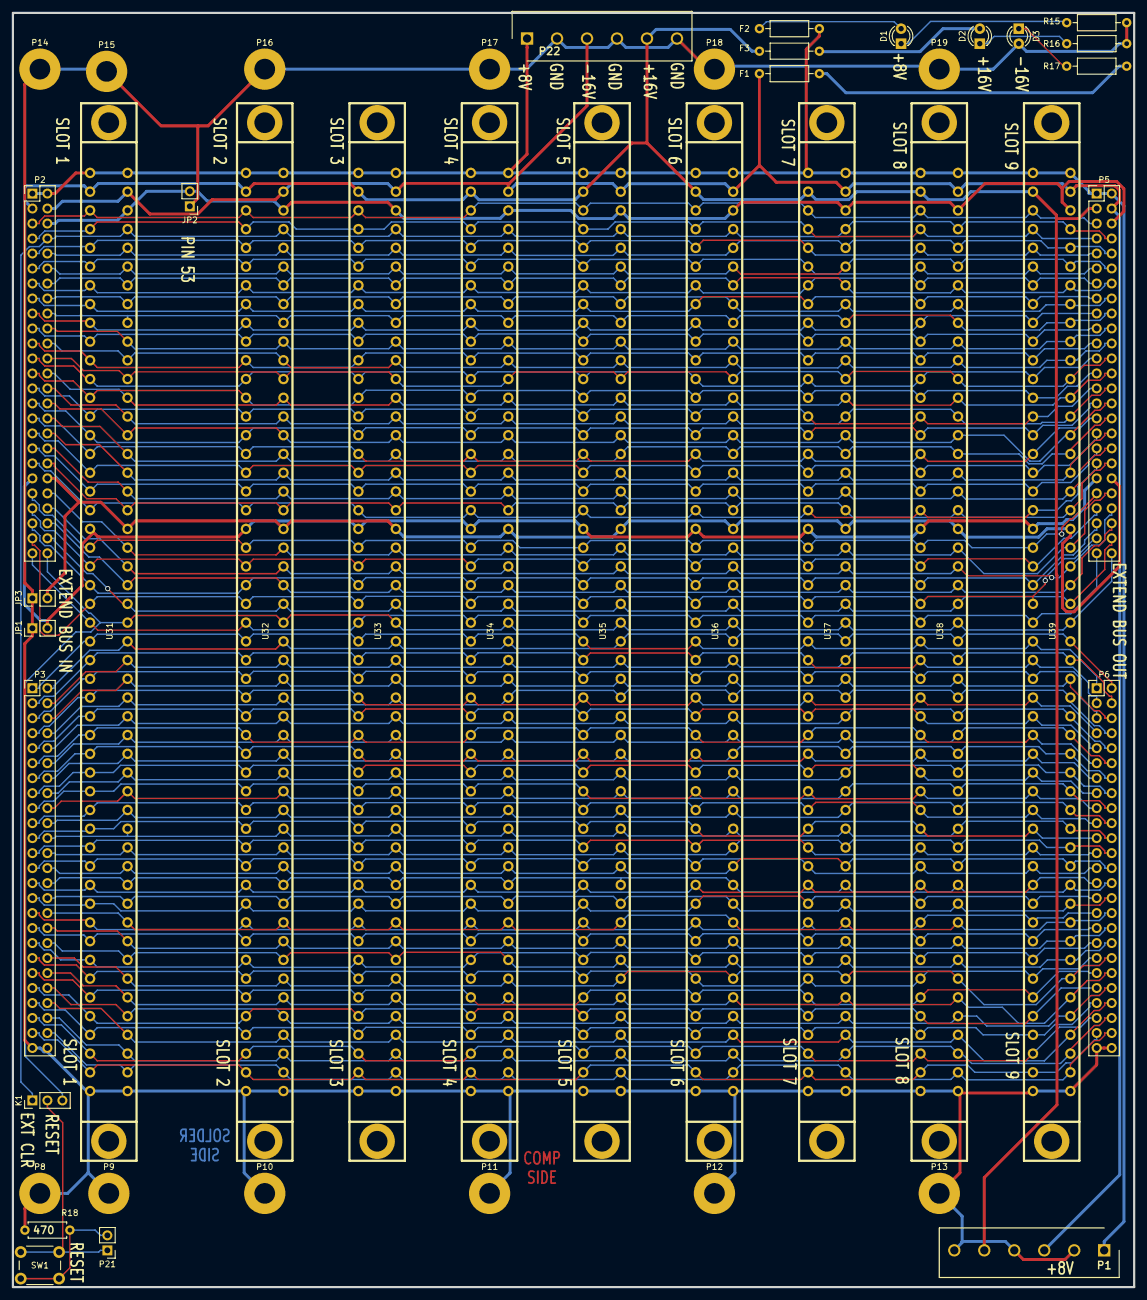
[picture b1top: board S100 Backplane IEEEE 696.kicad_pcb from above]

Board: 2 copper layers, 190.0 x 215.9 mm, 43 parts (0 on the bottom side), 106 nets.

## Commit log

2022-03-28 Add 1st attempt.
